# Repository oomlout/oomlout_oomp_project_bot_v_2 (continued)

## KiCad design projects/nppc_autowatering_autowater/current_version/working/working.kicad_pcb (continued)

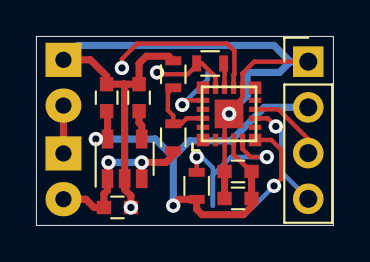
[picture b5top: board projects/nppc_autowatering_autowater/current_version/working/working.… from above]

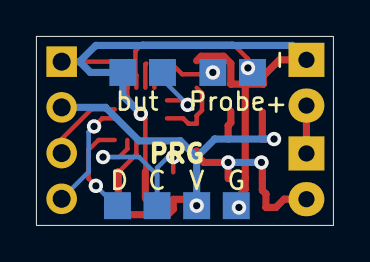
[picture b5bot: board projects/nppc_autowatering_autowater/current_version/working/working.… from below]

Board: 2 copper layers, 16.5 x 10.5 mm, 18 parts (4 on the bottom side), 14 nets.

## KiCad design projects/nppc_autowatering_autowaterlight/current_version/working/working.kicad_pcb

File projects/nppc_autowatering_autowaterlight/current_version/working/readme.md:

# autowatering
 
## summary 
* id: nppc_autowatering_autowaterlight
* user: nppc
* name: autowatering
* board: autowaterlight
* repo: https://github.com/nppc/AutoWatering
* src_file_repo_kicad_pcb: KiCad/AutoWaterLight/AutoWaterLight.kicad_pcb
* src_file_repo_kicad_pcb_link: https://github.com/nppc/AutoWatering/tree/master/KiCad/AutoWaterLight/AutoWaterLight.kicad_pcb

* src_file_repo_sch: KiCad/AutoWaterLight/AutoWaterLight.sch
* src_file_repo_sch_link: https://github.com/nppc/AutoWatering/tree/master/KiCad/AutoWaterLight/AutoWaterLight.sch
* full details link: https://github.com/oomlout/oomlout_oomp_project_bot_v_2/tree/main/projects/nppc_autowatering_autowaterlight/current_version/working

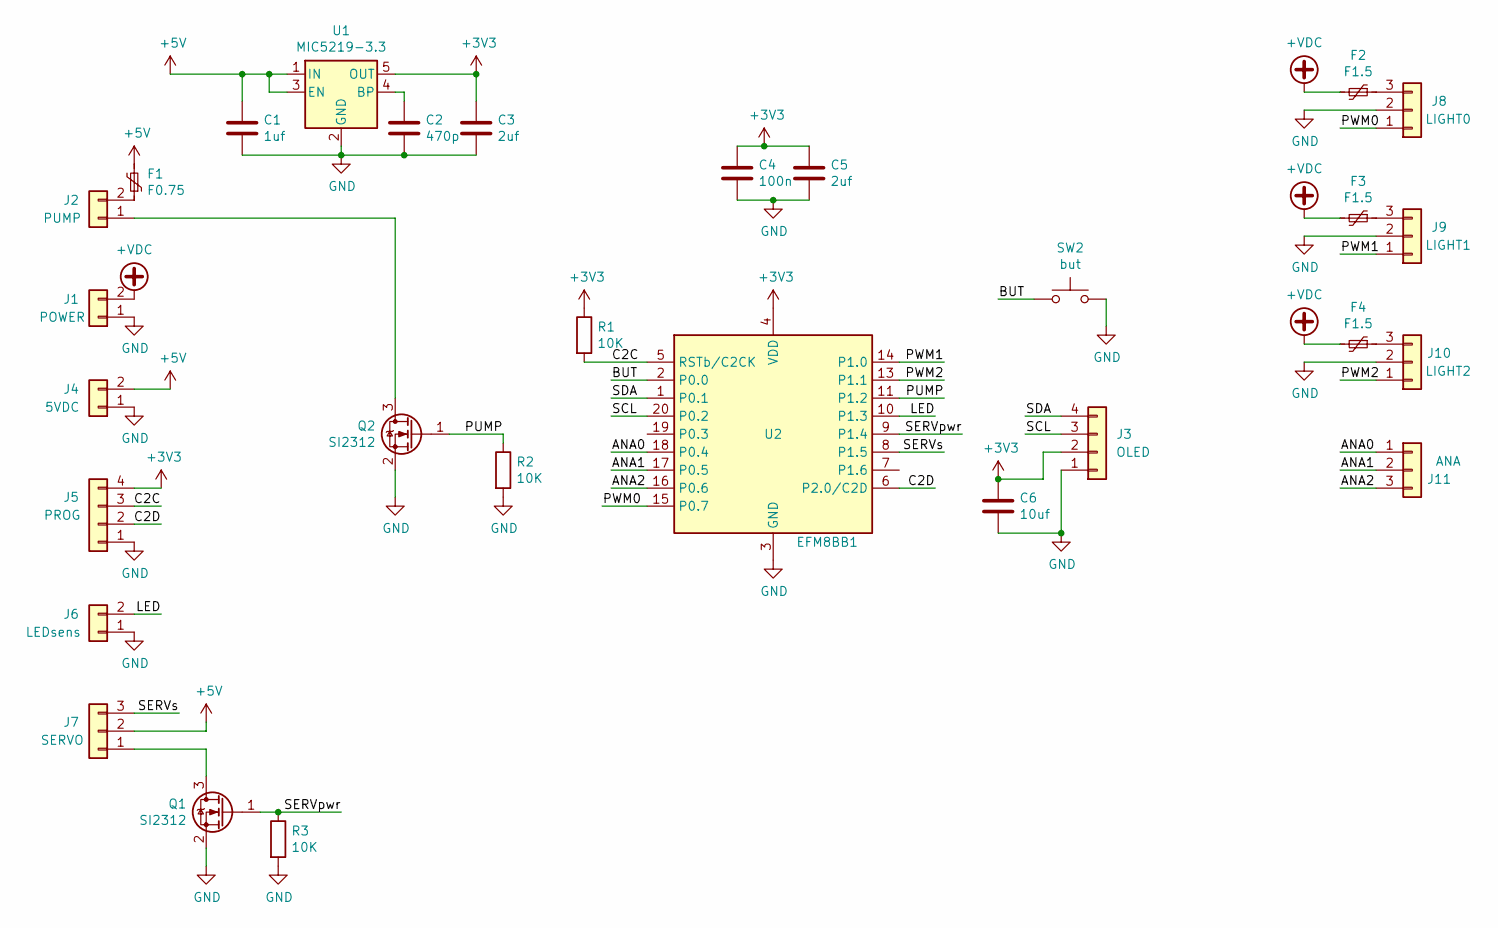
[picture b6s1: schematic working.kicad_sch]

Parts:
C1: 1uf; C_0603
C2: 470p; C_0603
C3, C5: 2uf; C_0603
C4: 100n; C_0603
C6: 10uf; C_0603
F1: F0.75; R_1812
F2, F3, F4: F1.5; R_1812
J1: POWER; Conn_Power
J2: PUMP; Conn_1x02_2.54_0.9mm
J3: OLED; Pin_Header_Straight_1x04_Pitch2.54mm
J4: 5VDC; Conn_1x02_2.54_0.9mm
J5: PROG; Molex_PicoBlade_53047-0410_04x1.25mm_Straight
J6: LEDsens; Conn_1x02_2.54_0.9mm
J7: SERVO; Conn_1x03_2.54mm
J8: LIGHT0; Conn_1x03_2.54mm
J9: LIGHT1; Conn_1x03_2.54mm
J10: LIGHT2; Conn_1x03_2.54mm
J11: ANA; PROG-3pin
Q1, Q2: SI2312; SOT-23
R1, R2, R3: 10K; R_0603
SW2: but; POWER2PIN_2
U1: MIC5219-3.3; SOT-23-5
U2: EFM8BB1; QFN20

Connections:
+3V3: C3.1, C4.1, C5.1, C6.1, J3.2, J5.4, R1.1, U1.5 (OUT), U2.4 (VDD)
+5V: C1.1, F1.2, J4.2, J7.2, U1.1 (IN), U1.3 (EN)
+VDC: F2.2, F3.2, F4.2, J1.2
/ANA0: J11.1, U2.18 (P0.4)
/ANA1: J11.2, U2.17 (P0.5)
/ANA2: J11.3, U2.16 (P0.6)
/BUT: SW2.1, U2.2 (P0.0)
/C2C: J5.3, R1.2, U2.5 (RSTb/C2CK)
/C2D: J5.2, U2.6 (P2.0/C2D)
/LED: J6.2, U2.10 (P1.3)
/PUMP: Q2.1 (G), R2.1, U2.11 (P1.2)
/PWM0: J8.1, U2.15 (P0.7)
/PWM1: J9.1, U2.14 (P1.0)
/PWM2: J10.1, U2.13 (P1.1)
/SCL: J3.3, U2.20 (P0.2)
/SDA: J3.4, U2.1 (P0.1)
/SERVpwr: Q1.1 (G), R3.1, U2.9 (P1.4)
/SERVs: J7.3, U2.8 (P1.5)
GND: C1.2, C2.2, C3.2, C4.2, C5.2, C6.2, J1.1, J3.1, J4.1, J5.1, J6.1, J8.2, J9.2, J10.2, Q1.2 (S), Q2.2 (S), R2.2, R3.2, SW2.2, U1.2 (GND), U2.3 (GND), U2.12 (GND), U2.21 (GND)
unnamed: C2.1, U1.4 (BP)
unnamed: F1.1, J2.2
unnamed: F2.1, J8.3
unnamed: F3.1, J9.3
unnamed: F4.1, J10.3
unnamed: J2.1, Q2.3 (D)
unnamed: J7.1, Q1.3 (D)

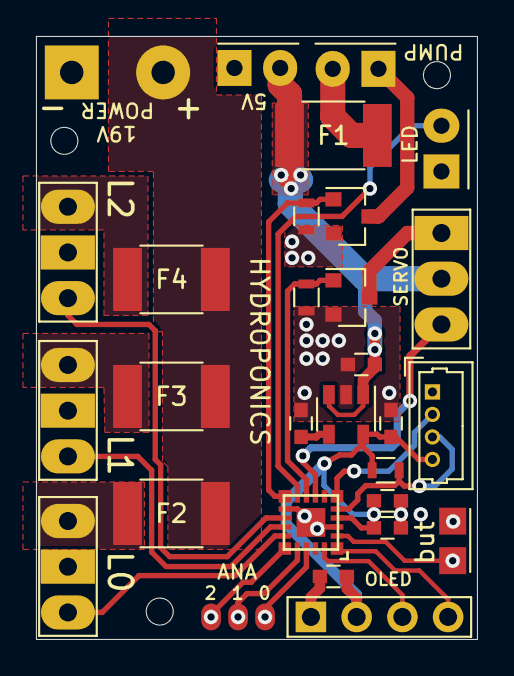
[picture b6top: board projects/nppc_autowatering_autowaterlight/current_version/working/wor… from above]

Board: 2 copper layers, 24.5 x 33.5 mm, 29 parts (0 on the bottom side), 26 nets.
